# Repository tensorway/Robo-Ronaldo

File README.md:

# Robonaldo

A robot designed to participate in RoboCup Junior Soccer Open competition.
It uses Lidar to position itself on the field and a rgb camera to search for the ball.

## to clone
cd into desired directory and clone it using:

<code> git clone https://github.com/tensorway/2020.git </code>

## to use it

<code> jupyter notebook </code>

the 2020 directory contains tutorials and examples.

## structure
esp32 directory contains microcontroler code
jupyter directory contains raspberry pi code
freecad directory contains freecad 3d models of the robot
pcb directory contains the pcb schematic which was manufactured

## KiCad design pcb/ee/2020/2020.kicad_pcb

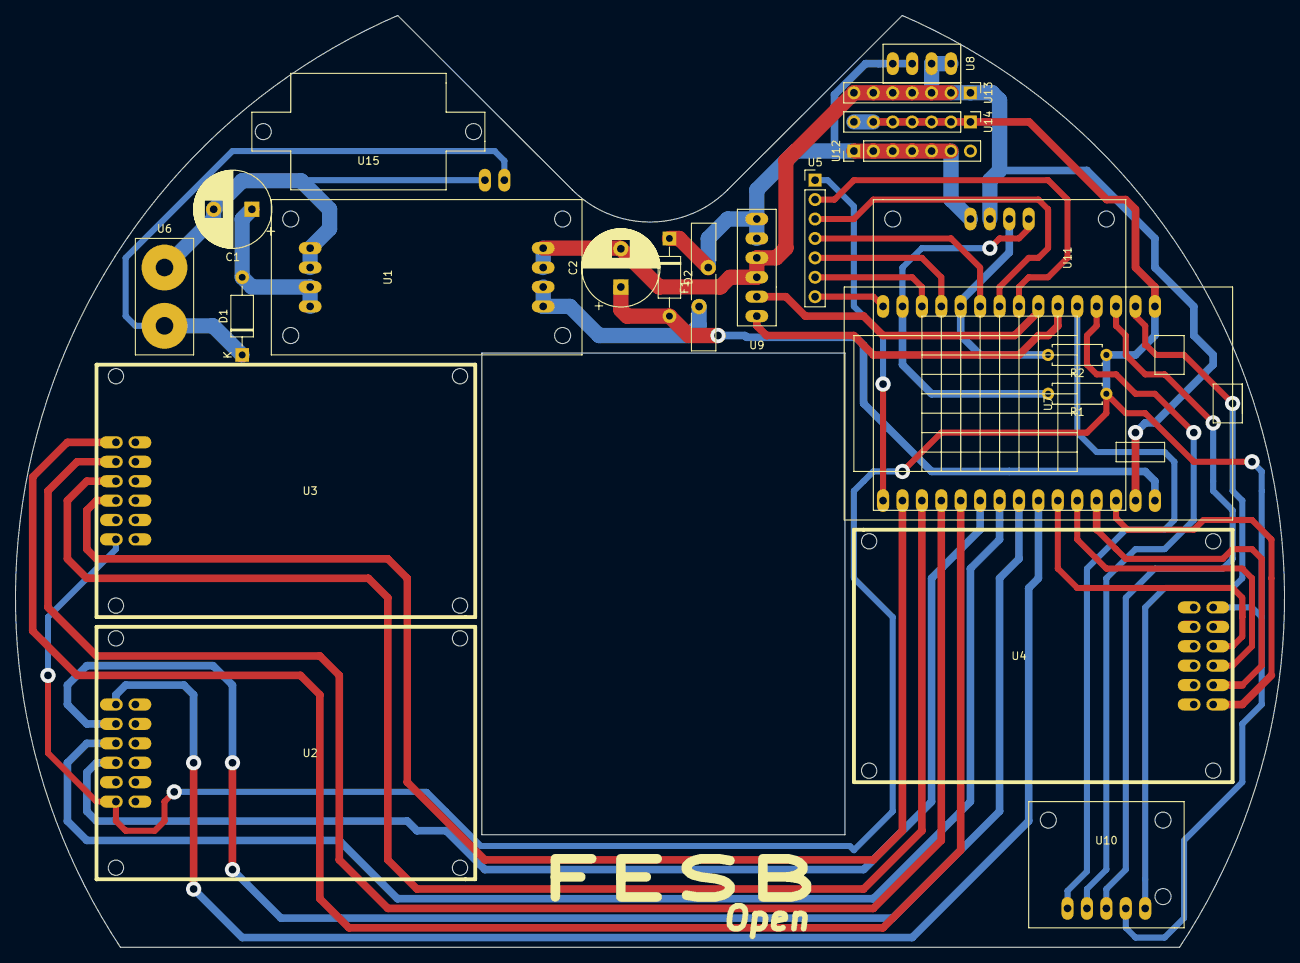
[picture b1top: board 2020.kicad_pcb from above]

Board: 2 copper layers, 166.0 x 121.9 mm, 22 parts (0 on the bottom side), 35 nets.

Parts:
C1, C2: CP_Small; CP_Radial_D10.0mm_P5.00mm
D1, D2: DIODE; D_A-405_P10.16mm_Horizontal
F1: Fuse; Fuse_Bourns_MF-RHT800
R1, R2: R_Small; R_Axial_DIN0207_L6.3mm_D2.5mm_P7.62mm_Horizontal
U1: 5V9A_regulator; 5V9A_REGULATOR
U2, U3, U4: motor_driver_2x125; mrm-mot2x125
U5: razvod_pinova; PinHeader_1x07_P2.54mm_Vertical
U6: INPUT_POWER
U7: ESP32
U8: RPLIDAR_A2
U9: RASPBERRY_PI4; raspberry_pi_4
U10: BNO055_ANALOG
U11: BICOLOR_LED_DISPLAY; BICOLOR_LED
U12: 5VS; PinHeader_1x07_P2.54mm_Vertical
U13: GNDS; PinHeader_1x07_P2.54mm_Vertical
U14: 3.3V; PinHeader_1x07_P2.54mm_Vertical
U15: VOLTMETER; voltmeter

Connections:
+5V: D2.1, F1.2, U8.0, U8.1, U9.0, U9.1, U11.3, U12.1, U12.2, U12.3, U12.4, U12.5, U12.6, U12.7
GND: C2.2, U1.0, U1.1, U7.16, U8.2, U8.3, U9.2, U9.3, U11.2, U13.1, U13.2, U13.3, U13.4, U13.5, U13.6, U13.7
unnamed: C1.1, D1.2, U1.6, U1.7
unnamed: C1.2, U1.4, U1.5, U6.0, U15.1
unnamed: C2.1, D2.2, U7.15
unnamed: D1.1, U6.1, U15.0
unnamed: F1.1, U1.2, U1.3
unnamed: R1.1, R2.1, U2.5, U3.5, U4.5, U7.0, U10.3, U14.1, U14.2, U14.3, U14.4, U14.5, U14.6, U14.7
unnamed: R1.2, U7.13, U11.0
unnamed: R2.2, U7.10, U11.1
unnamed: U2.0, U7.21
unnamed: U2.1, U7.22
unnamed: U2.2, U7.23
unnamed: U2.3, U7.24
unnamed: U3.0, U7.25
unnamed: U3.1, U7.26
unnamed: U3.2, U7.27
unnamed: U3.3, U7.28
unnamed: U4.0, U7.17
unnamed: U4.1, U7.18
unnamed: U4.2, U7.19
unnamed: U4.3, U7.20
unnamed: U5.1, U7.29
unnamed: U5.2, U7.7
unnamed: U5.3, U7.8
unnamed: U5.4, U7.9
unnamed: U5.5, U7.11
unnamed: U5.6, U7.12
unnamed: U5.7, U7.14
unnamed: U7.5, U9.5
unnamed: U7.6, U9.4
unnamed: U7.4, U10.0
unnamed: U7.3, U10.1
unnamed: U7.2, U10.2
unnamed: U7.1, U10.4

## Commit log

2020-02-16 initial state commit
2020-02-21 removed redundant jupyter folder experimented with resolution for ball findig (Untitled6)
    Untitled6 in opencv now has image parameters frozen, and works at various
    resolution
2020-02-21 renamed Untitled6 to image_parameters_lock
2020-02-26 diff tests in param lock
2020-03-04 vision now works on picamera + mask that tells what is not ball
    vision is on picamera and iso, exposure, white ballance can be controlled
    if there is no ball near robot it can now threshold everything and
    see what is definitelly not ball
2020-03-14 it now detect the field and excludes everything outside
    in convexity test /opencv detects green and makes shape convex calculates
    mask and uses that mask for detection
2020-03-15 ball detection works now from centre of the field to anywhere.
2020-09-13 added some tutorials
2020-09-14 added lidar, camera and all together
2020-09-14 removed trash items
2020-09-14 added readme explanation
2020-09-14 deleted trash
2020-10-08 added gif
2021-10-01 to english
2021-10-01 typo
